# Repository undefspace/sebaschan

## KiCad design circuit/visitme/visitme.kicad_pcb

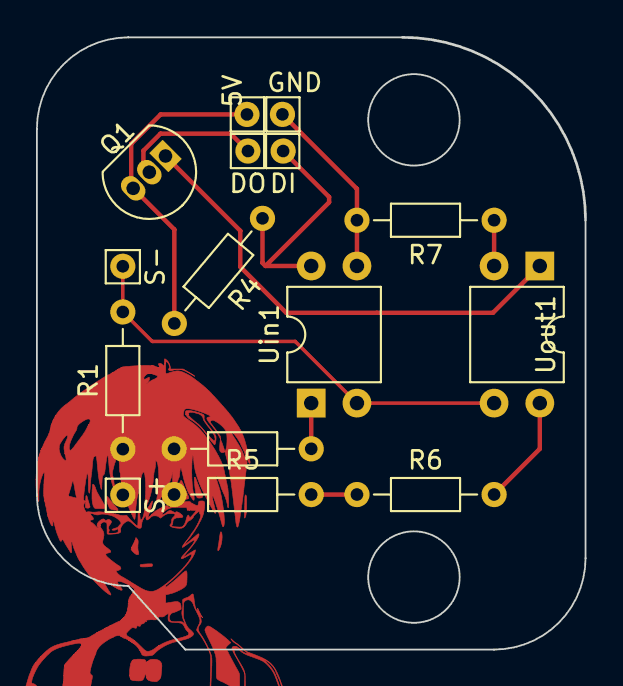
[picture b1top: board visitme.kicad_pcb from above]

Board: 2 copper layers, 30.5 x 34.0 mm, 15 parts (0 on the bottom side), 11 nets.

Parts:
5V: Conn_01x01_Female; Pin_D0.7mm_L6.5mm_W1.8mm_FlatFork
DI: Conn_01x01_Female; Pin_D0.7mm_L6.5mm_W1.8mm_FlatFork
DO: Conn_01x01_Female; Pin_D0.7mm_L6.5mm_W1.8mm_FlatFork
GND: Conn_01x01_Female; Pin_D0.7mm_L6.5mm_W1.8mm_FlatFork
Q1: BC237; TO-92_Inline
R1: 4.7k; R_Axial_DIN0204_L3.6mm_D1.6mm_P7.62mm_Horizontal
R2: 6.8k; R_Axial_DIN0204_L3.6mm_D1.6mm_P7.62mm_Horizontal
R4: 10k; R_Axial_DIN0204_L3.6mm_D1.6mm_P7.62mm_Horizontal
R5: 10; R_Axial_DIN0204_L3.6mm_D1.6mm_P7.62mm_Horizontal
R6: 47; R_Axial_DIN0204_L3.6mm_D1.6mm_P7.62mm_Horizontal
R7: 22; R_Axial_DIN0204_L3.6mm_D1.6mm_P7.62mm_Horizontal
S+: Conn_01x01_Female; Pin_D0.7mm_L6.5mm_W1.8mm_FlatFork
S-: Conn_01x01_Female; Pin_D0.7mm_L6.5mm_W1.8mm_FlatFork
Uin1: PC817; DIP-4_W7.62mm
Uout1: PC817; DIP-4_W7.62mm

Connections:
+5V: 5V.1, Q1.3 (E), R4.2
D2 Data In: DI.1, R4.1, Uin1.4
D6 Data Out: DO.1, Q1.2 (B)
GND: GND.1, R7.2, Uin1.3
unnamed: Q1.1 (C), Uout1.1
unnamed: R2.2, Uin1.1
unnamed: R5.2, R6.1
unnamed: R6.2, Uout1.4
unnamed: R7.1, Uout1.2
Signal+: R1.1, R2.1, R5.1, S+.1
Signal-: R1.2, S-.1, Uin1.2, Uout1.3

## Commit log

2021-03-25 secretified everything
2021-03-26 Add 1 git-crypt collaborator
    New collaborators:
    38C711DC Eugenia Vaartis <97nomad@gmail.com>
2021-06-21 hacking through the gate
2021-09-20 switched to open_drain pin mode, added counter
2023-04-03 added circuit
2023-04-03 removed redundant 470k
2023-04-03 further board refinement
2023-07-05 Add 1 git-crypt collaborator
    New collaborators:
    DC1AA233 Anna Antonenko <hi@portasynthinca3.me>
